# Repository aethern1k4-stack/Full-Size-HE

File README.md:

Full-Size-HE
------------------------------------------------------------------------
Layout
first row -13 keys - esc no function row or hotkeys
2 encoders for volume top right and tap shift or window shift
60% mainframe
arrow keys + numpad on right side
60+12+10+1 encoder
82 keys total
84/16=6 multiplexers
------------------------------------------------------------------------
Bill Of Materials (BOM):
- SS39ET Hall Effect Sensors - around 82
- CD74HC4067M - subject to change
- NRF52840 chipset- will find cheaper reatailer if possible - xiao nrf plus - AqFN package
- ADS7953 - 2
- Stabilisers
- Bunch of other passive componenets like caps and resitors and inductors will go with jlc pcb hopefully is pretty cheap or else im cooked
- Sidenote : make this a table
------------------------------------------------------------------------
Links to parts:
- https://www.aliexpress.com/item/32947763024.html?src=google&src=google&albch=shopping&acnt=494-037-6276&isdl=y&slnk=&plac=&mtctp=&albbt=Google_7_shopping&aff_platform=google&aff_short_key=UneMJZVf&gclsrc=aw.ds&albagn=888888&ds_e_adid=&ds_e_matchtype=&ds_e_device=c&ds_e_network=x&ds_e_product_group_id=&ds_e_product_id=en32947763024&ds_e_product_merchant_id=106352398&ds_e_product_country=GB&ds_e_product_language=en&ds_e_product_channel=online&ds_e_product_store_id=&ds_url_v=2&albcp=17859500389&albag=&isSmbAutoCall=false&needSmbHouyi=false&gad_source=1&gad_campaignid=17190468917&gbraid=0AAAAADznYb-jgfaMP0pVJpa3NxUnI1EPb&gclid=CjwKCAjwtIfPBhAzEiwAv9RTJgP07K0X9OdHAwVdgm_r8G4068To99SZJrdk_1ppE7nolsXXjeVjchoCHh4QAvD_BwE
- https://www.aliexpress.com/item/1005010737380882.html?src=google&src=google&albch=shopping&acnt=494-037-6276&isdl=y&slnk=&plac=&mtctp=&albbt=Google_7_shopping&aff_platform=google&aff_short_key=UneMJZVf&gclsrc=aw.ds&albagn=888888&ds_e_adid=&ds_e_matchtype=&ds_e_device=c&ds_e_network=x&ds_e_product_group_id=&ds_e_product_id=en1005010737380882&ds_e_product_merchant_id=107720701&ds_e_product_country=GB&ds_e_product_language=en&ds_e_product_channel=online&ds_e_product_store_id=&ds_url_v=2&albcp=17859500389&albag=&isSmbAutoCall=false&needSmbHouyi=false&gad_source=1&gad_campaignid=17190468917&gbraid=0AAAAADznYb94JGR3QLxcjWmKwQXFd6cLL&gclid=CjwKCAjw14zPBhAuEiwAP3-Eb_XqaDXgcy4JyoVUt9kZnHWvkaZzNkuUYnO8bQ_t_kHBOzVO1QHGyxoCJFoQAvD_BwE
- https://www.mouser.co.uk/ProductDetail/Espressif-Systems/ESP32-S3-DevKitC-1-N8R8?qs=7D1LtPJG0i2PiuUUKucutQ%3D%3D&mgh=1&vip=1&srsltid=AfmBOopMvMwdzu8ST-6wfS-dXYGPuxZugr3CFNqxJotEgJbmLgow9ZHmNHg
- https://www.ebay.co.uk/itm/397492465002?_skw=j+link+edu+mini&itmmeta=01KQG7ARJ7X8TBB1AF0PWW50DK&hash=item5c8c65ad6a:g:RhEAAeSwJOlpZsr2&itmprp=enc%3AAQALAAAA8GfYFPkwiKCW4ZNSs2u11xAZcMiQqBqE3PIVQwD2O7Ge55XLWpKOyoquYGIvs3U719LdG8tDOE9z3PO1ZqPy3KUPIfdRcKeFEG4GBbAEdgeCuoPcCrVu9qx%2FBhTNhHck%2F0JtBxYyetdLv1oUiFh2lRnBE84%2Bs5zT68ujv3Bd5grrYpKE8LEb7UF9Yd7YSrrLHX%2FQJrv8k2pPpG2N1kaU0vq%2F9y1exSGPfR8kXVVDgwEsxE4SpTTvB58lBTXXkGRtV7R37SHeGuZF8bgNsUxivb21crRB3SCSR91jsZIbweMO8AUdjLYO0%2B5UWBIMA450yA%3D%3D%7Ctkp%3ABk9SR7iJq4e8Zw
------------------------------------------------------------------------
Research for this project is till in progress
Research was assisted by Claude AI to search for datasheets and other misc tasks as well as cost optimisation

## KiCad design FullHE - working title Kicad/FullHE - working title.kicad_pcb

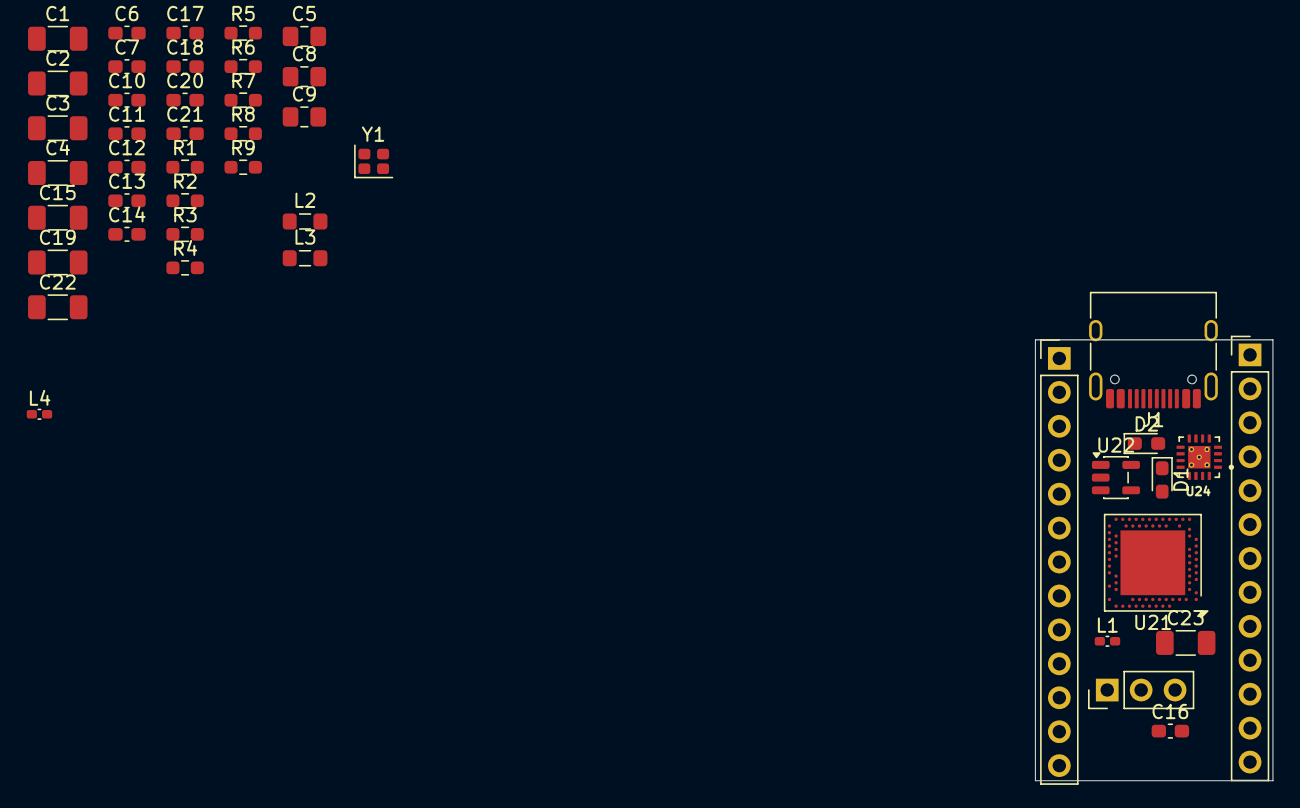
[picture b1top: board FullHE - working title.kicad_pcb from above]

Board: 2 copper layers, 17.8 x 33.0 mm, 44 parts (1 on the bottom side), 33 nets, no tracks yet.

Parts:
C1: 10uF; C_1206_3216Metric_Pad1.33x1.80mm_HandSolder
C2, C3, C4, C15, C19, C22, C23: 4.7uF; C_1206_3216Metric_Pad1.33x1.80mm_HandSolder
C5: 1uF; C_0805_2012Metric_Pad1.18x1.45mm_HandSolder
C6, C7: 12pF; C_0603_1608Metric_Pad1.08x0.95mm_HandSolder
C8, C9: 1pF; C_0805_2012Metric_Pad1.18x1.45mm_HandSolder
C10: 1.5pF; C_0603_1608Metric_Pad1.08x0.95mm_HandSolder
C11, C12, C13, C16, C17: 100nF; C_0603_1608Metric_Pad1.08x0.95mm_HandSolder
C14, C20: 1uF; C_0603_1608Metric_Pad1.08x0.95mm_HandSolder
C18: 820pF; C_0603_1608Metric_Pad1.08x0.95mm_HandSolder
C21: 47nF; C_0603_1608Metric_Pad1.08x0.95mm_HandSolder
D1: BLUE; LED_0603_1608Metric_Pad1.05x0.95mm_HandSolder
D2: ORANGE; LED_0603_1608Metric_Pad1.05x0.95mm_HandSolder
J1: USB_C_Receptacle_USB2.0_16P; USB_C_Receptacle_HRO_TYPE-C-31-M-12
JP1: Jumper_2_Open; SolderJumper-2_P1.3mm_Open_RoundedPad1.0x1.5mm
L1: 3.9nH; L_0402_1005Metric_Pad0.77x0.64mm_HandSolder
L2, L3: 10uH; L_0805_2012Metric_Pad1.05x1.20mm_HandSolder
L4: 15nH; L_0402_1005Metric_Pad0.77x0.64mm_HandSolder
R1: 1k; R_0603_1608Metric_Pad0.98x0.95mm_HandSolder
R2, R3: 5.1k; R_0603_1608Metric_Pad0.98x0.95mm_HandSolder
R4: 10M; R_0603_1608Metric_Pad0.98x0.95mm_HandSolder
R5, R6, R7: 10k; R_0603_1608Metric_Pad0.98x0.95mm_HandSolder
R8: 2k; R_0603_1608Metric_Pad0.98x0.95mm_HandSolder
R9: 0; R_0603_1608Metric_Pad0.98x0.95mm_HandSolder
U21: nRF52840; Nordic_AQFN-73-1EP_7x7mm_P0.5mm
U22: XC6220B331MR; SOT-23-5
U24: BQ24072RGT; IC_BQ24072RGTT
Y1: 32MHz XRCGB32M000F1H50R0; Crystal_SMD_2016-4Pin_2.0x1.6mm

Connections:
ANTENNA: C10.1, R9.1
BLED: D1.2 (A), U21.AD10 (P0.15)
D+: J1.A6 (D+), J1.B6 (D+), U21.AD6 (D+)
D-: J1.A7 (D-), J1.B7 (D-), U21.AD4 (D-)
EXT_VCC: C2.2, U22.5 (VOUT)
GND: C1.1, C2.1, C3.2, C4.2, C5.2, C6.2, C7.2, C9.2, C10.2, C11.2, C12.2, C13.2, C14.2, C15.2, C16.2, C17.2, C18.1, C19.1, C20.1, C21.1, C22.2, C23.2, J1.A1 (GND), J1.A12 (GND), J1.B1 (GND), J1.B12 (GND), R1.2, R2.2, R3.2, R6.2, R7.2, R8.2, U22.2 (GND), U24.4 (~CE), U24.5 (EN2), U24.8 (VSS), U24.15 (SYSOFF), U24.17 (PAD), Y1.2
unnamed: C9.1, L1.1, R9.2
unnamed: D1.1 (K), R1.1
unnamed: D2.2 (A), R5.1
unnamed: D2.1 (K), U24.9 (~CHG)
unnamed: J1.A5 (CC1), R2.1
unnamed: J1.B5 (CC2), R3.1
unnamed: JP1.1 (A), R7.1, U24.16 (ISET)
unnamed: JP1.2 (B), R8.1
unnamed: L2.1, L4.2
unnamed: C8.1, L1.2, U21.H23 (ANT)
unnamed: L2.2, U21.B3 (DCC)
unnamed: L3.1, U21.AB2 (DCCH)
unnamed: C17.1, U21.C1 (DEC1)
unnamed: C16.1, U21.D23 (DEC3)
unnamed: C20.2, C21.2, L4.1, U21.B5 (DEC4), U21.E24 (DEC6)
unnamed: C18.2, U21.N24 (DEC5)
unnamed: C19.2, U21.AC5 (DECUSB)
unnamed: U21.B7 (VSS), U21.EP (VSS)
unnamed: C6.1, U21.B24 (XC1), Y1.1
unnamed: C7.1, U21.A23 (XC2), Y1.3
unnamed: R6.1, U24.1 (TS)
POWER_PIN: R4.2, U21.AD8 (P0.13), U22.3 (CE)
RESET: U21.AC9 (P0.14), U21.AC11 (P0.16), U21.AC13 (P0.18/~RESET), U21.H2 (P0.27)
VBAT: C3.1, U24.2 (BAT), U24.3 (BAT)
VBUS: C5.1, C22.1, J1.A4 (VBUS), J1.A9 (VBUS), J1.B4 (VBUS), J1.B9 (VBUS), U21.AD2 (VBUS), U24.13 (IN)
VDDH: C1.2, C4.1, C23.1, R4.1, R5.2, U21.Y2 (VDDH), U22.1 (VIN), U24.6 (EN1), U24.10 (OUT), U24.11 (OUT)
VDD_NRF: C11.1, C12.1, C13.1, C14.1, C15.1, L3.2, U21.A22 (VDD), U21.AD14 (VDD), U21.AD23 (VDD), U21.B1 (VDD), U21.W1 (VDD)

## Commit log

2026-04-24 KICAD files addition
